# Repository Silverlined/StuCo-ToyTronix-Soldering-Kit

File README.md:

# ToyTronix Student Company - Soldering Kit

ToyTronix - a soldering kit for young children. The idea was inspired by [Shawn Hymmel's 555 timer badge](https://twitter.com/oshpark/status/1000262755927064576). I worked through the whole process of design to production.

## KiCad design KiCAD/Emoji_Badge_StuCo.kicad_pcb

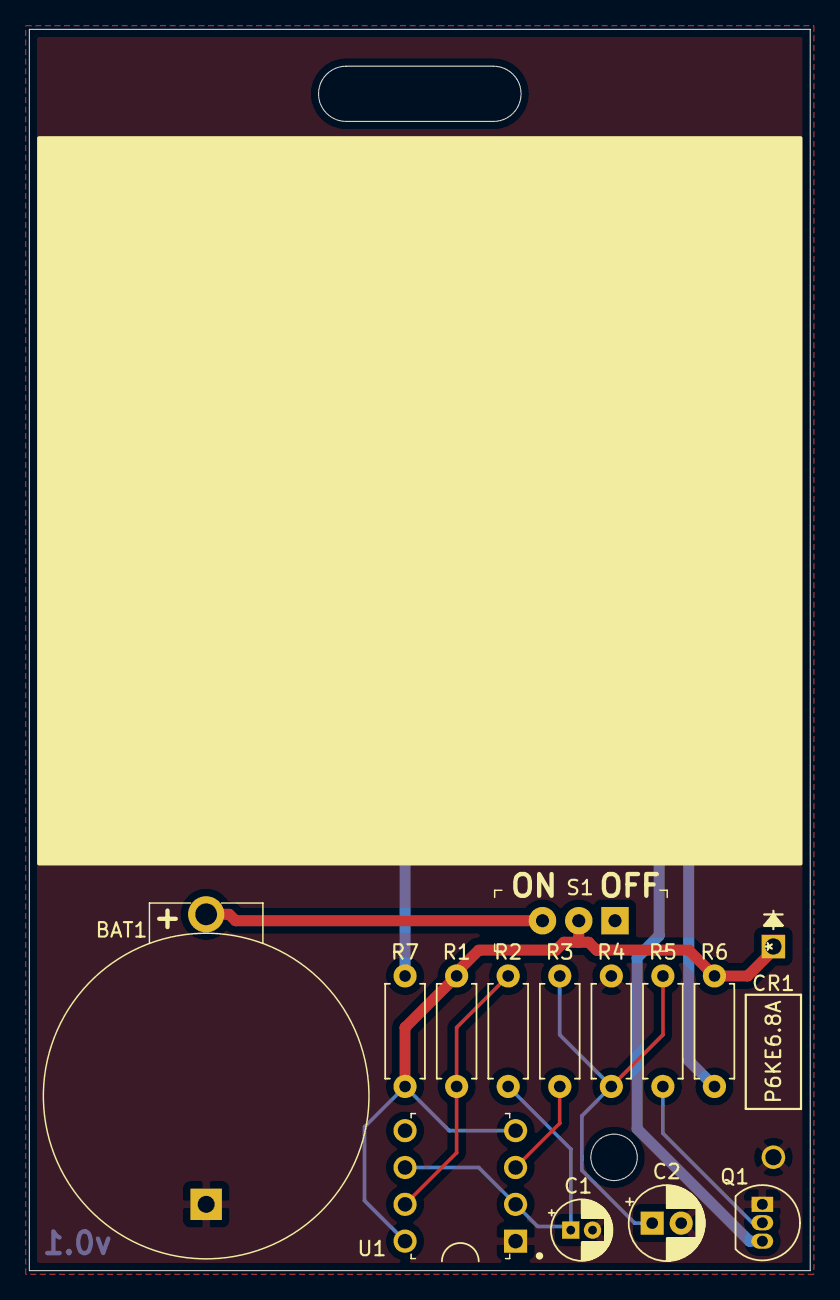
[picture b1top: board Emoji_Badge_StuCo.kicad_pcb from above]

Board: 2 copper layers, 53.8 x 85.6 mm, 16 parts (0 on the bottom side), 11 nets.

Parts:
BAT1: BS-7; Battery_Holder_Coin_2032_BS-7
C1: 10uF; CP_Radial_D4.0mm_P1.50mm
C2: 100uF; CP_Radial_D5.0mm_P2.00mm
CR1: P6KE6.8A
D1, D2: LED; LED_D3.0mm
Q1: 2N3904; TO-92_Inline
R1, R3: 22k; R_Axial_DIN0207_L6.3mm_D2.5mm_P7.62mm_Horizontal
R2: 330k; R_Axial_DIN0207_L6.3mm_D2.5mm_P7.62mm_Horizontal
R4: 100k; R_Axial_DIN0207_L6.3mm_D2.5mm_P7.62mm_Horizontal
R5: 10k; R_Axial_DIN0207_L6.3mm_D2.5mm_P7.62mm_Horizontal
R6, R7: 100; R_Axial_DIN0207_L6.3mm_D2.5mm_P7.62mm_Horizontal
S1: EG1218; Switch_Slide_11.6x4mm_EG1218
U1: ICM7555IPAZ; DIP-8_W7.62mm

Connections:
DISCH: R1.2, R2.1, U1.7
GND: BAT1.Neg, C1.2, C2.2, CR1.2, Q1.1, R4.1, U1.1
unnamed: BAT1.Pos, S1.3
unnamed: C1.1, R2.2, U1.2, U1.6
unnamed: C2.1, R3.1, R4.2, R5.1
unnamed: D1.1, D2.1, Q1.3
unnamed: D1.2, R6.2
unnamed: D2.2, R7.2
unnamed: Q1.2, R5.2
unnamed: R3.2, U1.3
VCC: CR1.1, R1.1, R6.1, R7.1, S1.2, U1.4, U1.8

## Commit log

2021-03-31 Init commit
2021-03-31 Refactoring
2021-03-31 Replace misc
